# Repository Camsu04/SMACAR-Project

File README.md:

# SMACAR-Project 

**SMACAR: SISTEMA DE MONITOREO Y ALERTA DE CALIDAD DEL AGUA RURAL**

Plataforma distribuida de monitoreo de calidad de agua diseñada para entornos rurales: cada nodo utiliza un ESP32 programado íntegramente en C que adquiere parámetros críticos (pH, turbidez, conductividad y temperatura) mediante sensores industriales. La comunicación se realiza vía LoRaWAN, asegurando transmisión de datos robusta, segura y de largo alcance hacia una interfaz web/móvil de acceso remoto. El sistema opera con energía renovable, priorizando autonomía y bajo mantenimiento. El diseño prioriza robustez, escalabilidad y validación científica, permitiendo despliegue inmediato, integración con infraestructuras existentes y generación automatizada de alertas para respuesta temprana ante riesgos sanitarios.

---

## 🌟 Vista rápida

### Diseño del sistema

---

### Prototipo físico armado

Coming soon...
// 

---

### Electronica

| PCB TRANSMISOR                            | PCB RECEPTOR                               |
|-------------------------------------------|--------------------------------------------|
|  |  |

---

### Carcasa 3D 

| Transmisor y sensores                     | RECEPTOR                                   |
|-------------------------------------------|--------------------------------------------|
|  |  |

---

### Diseño 3D animado

---

### App móvil

| Pantalla principal | App en funcionamiento |
|--------------------|----------------------|
|  |  |

### DASHBOARD WEB

---

### Diagrama de Flujo

| Transmisor | Receptor                     |
|--------------------|----------------------|
| .png) | .png) |

---

## 📁 Estructura del repositorio

```
SMACAR-Project/
├── Documentacion/           # Diagramas, fotos y GIFs de diseño
│   ├── Layout.png
│   ├── CARCASA.jpg
│   ├── DIAGRAMA.pdf
│   ├── DATASHEET.pdf
│   ├── PROYECTO FINAL.jpg
├── Hardware/                # Archivos y esquemas electrónicos + Diseños 3d en solidworks
├── Software firmware/       # Código fuente para ESP32 y LoRa
├── mobile app/              # Capturas de la app móvil
│   ├── APP.jpg
│   ├── APP MOBILE EN FUNCIONAMIENTO.jpg
├── LICENSE
└── README.md
```

---

## 🚀 ¿Cómo empezar?

1. **Clona el repositorio:**
    ```bash
    git clone https://github.com/Camsu04/SMACAR-Project.git
    cd SMACAR-Project
    ```

2. **Revisa los esquemas y fotos** en la carpeta `Documentacion/`.

3. **Carga el firmware** desde `Software firmware/` a tu ESP32 usando [ESP-IDF](https://docs.espressif.com/projects/esp-idf/en/latest/esp32/get-started/index.html).

4. **Configura los sensores** (pH, turbidez, TDS) según el diseño mostrado y alimenta el sistema (idealmente con energía solar).

5. **Visualiza los datos** usando la app móvil incluida.

---

## ⚡ Características

- Sistema modular, autónomo y robusto
- Monitoreo de agua en tiempo real
- Notificaciones y visualización desde tu móvil
- Carcasa resistente impresa en 3D
- Bajo consumo y operación solar
- Fácil de instalar y ampliar

---

## 🛠️ Requisitos

- **ESP32**
- Sensores de pH, turbidez,temperatura y TDS
- Módulo LoRa (compatible ESP32)
- Fuente solar o alimentación adecuada (3.3v o 5v)
- Teléfono Android para la app móvil

---

## 📲 App móvil

Encuentra las capturas y funcionamiento en la carpeta `mobile app/`.
La app permite visualizar datos de los sensores, recibir alertas y consultar el historial.

---

## 🤝 Contribuciones

¿Tienes ideas o mejoras?
- Abre un *Issue* para dudas o bugs
- Haz un *Pull Request* si mejoras el código, documentación o la app móvil

---

## 📄 Licencia

Proyecto bajo licencia MIT.
Consulta el archivo [LICENSE](LICENSE).

---

## 👨‍💻 Autores

- [Camsu04](https://github.com/Camsu04)
- [Fausto123f](https://github.com/Fausto123f)
- [j0nfut](https://github.com/j0nfut)
- [RiQ4](https://github.com/RiQ4)

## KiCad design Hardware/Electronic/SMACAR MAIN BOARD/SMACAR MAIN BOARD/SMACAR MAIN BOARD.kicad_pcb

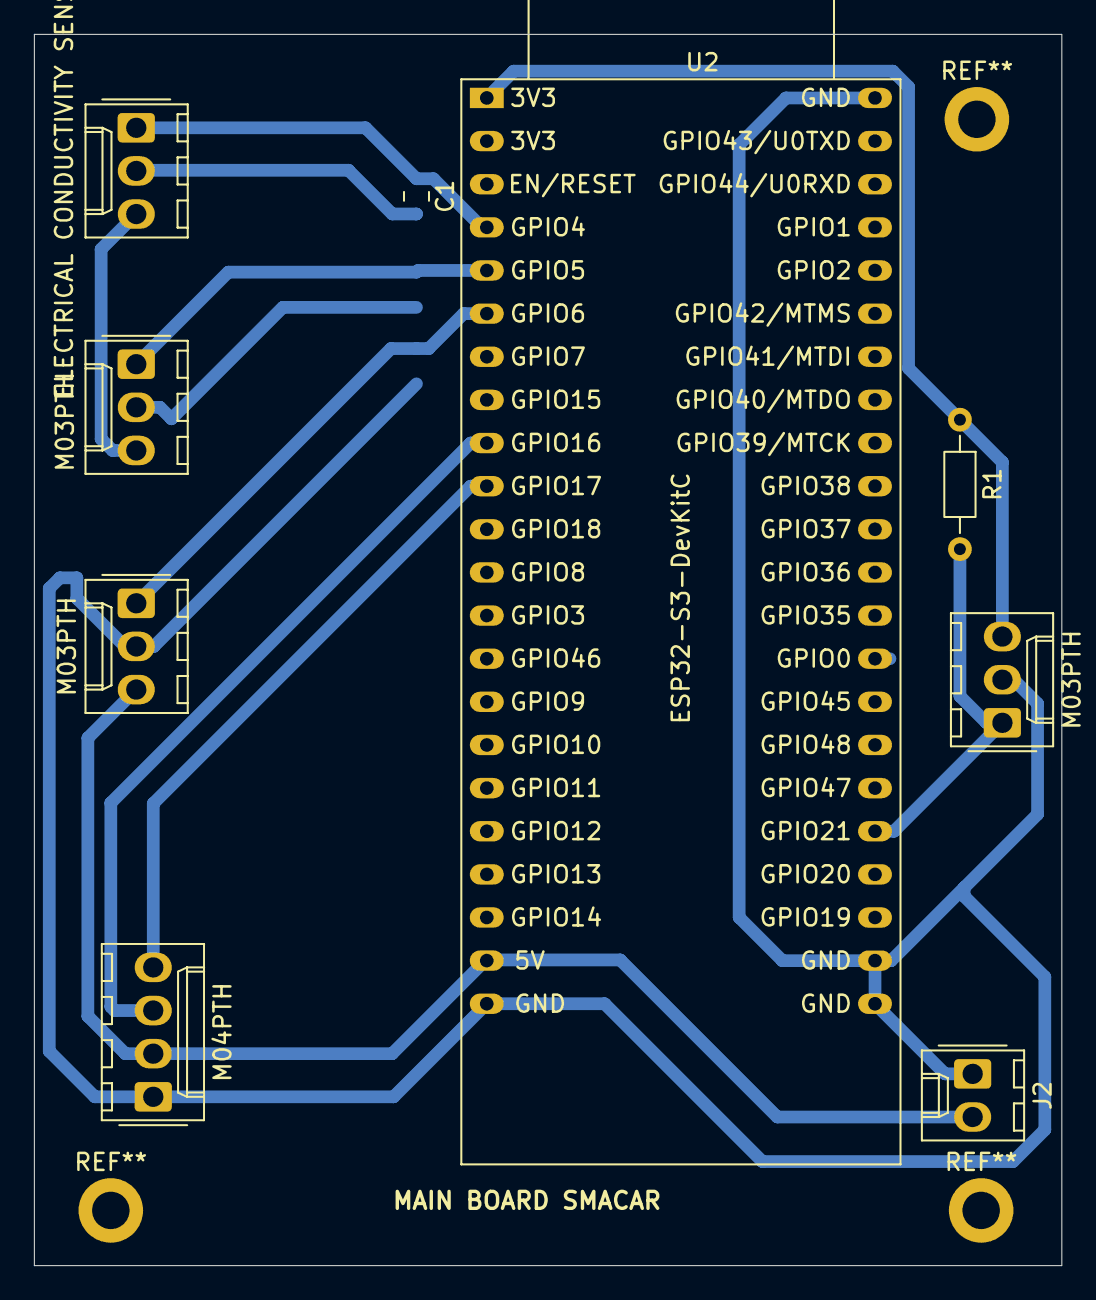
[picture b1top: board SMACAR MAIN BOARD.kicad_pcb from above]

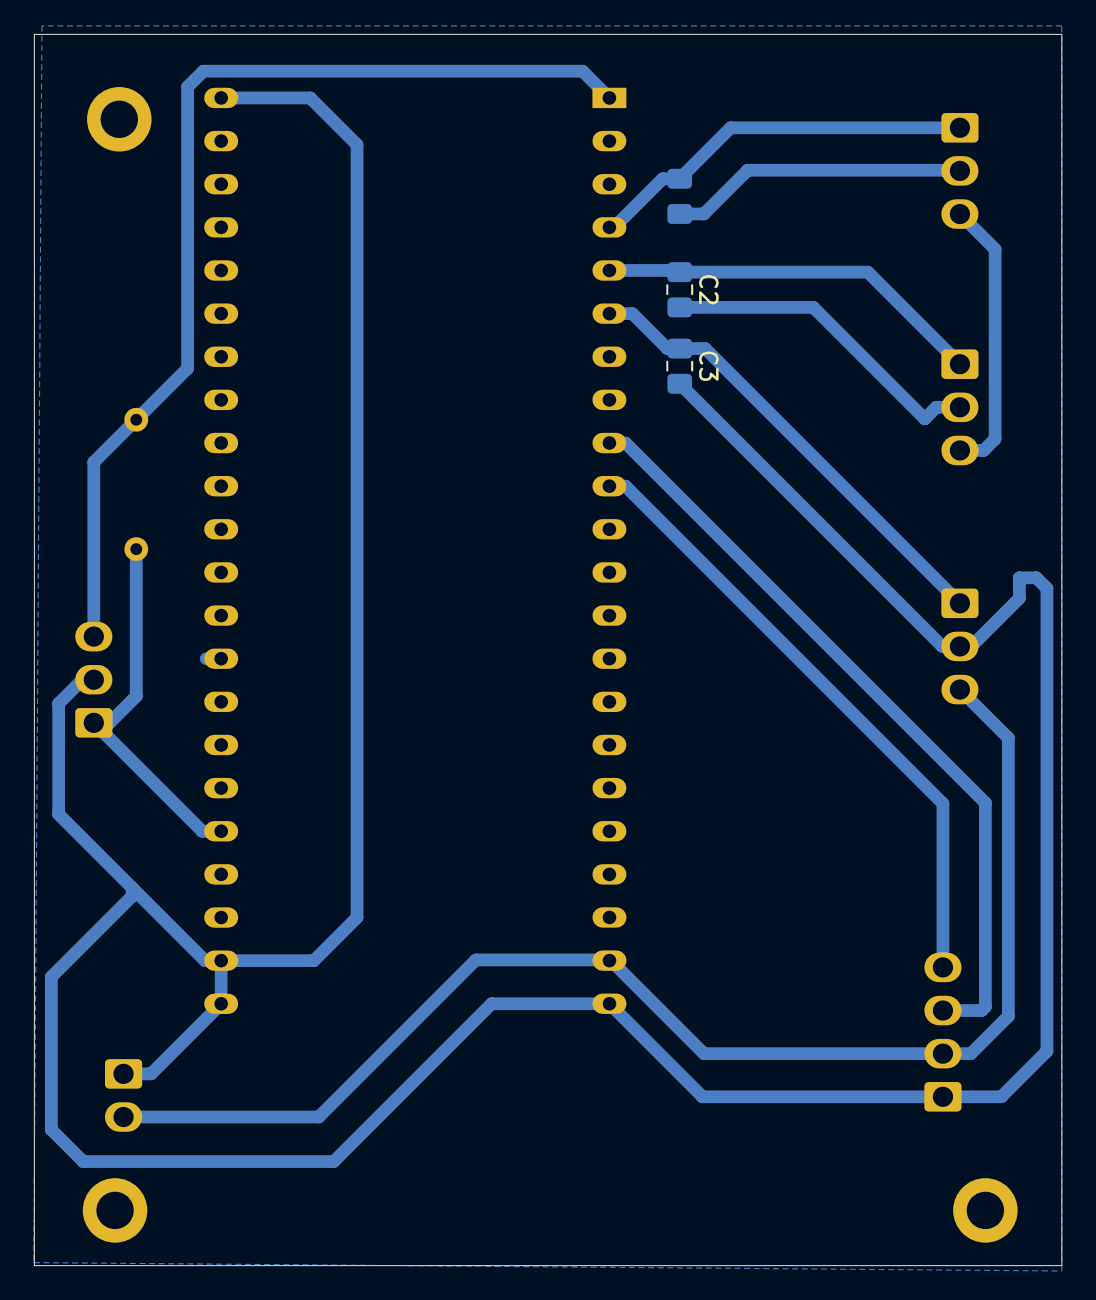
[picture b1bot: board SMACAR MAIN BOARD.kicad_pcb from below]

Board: 2 copper layers, 60.5 x 72.5 mm, 11 parts (2 on the bottom side), 9 nets.

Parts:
C1, C2, C3: 100nF_Ceramic; C_0805_2012Metric_Pad1.18x1.45mm_HandSolder
J2: Conn_01x02; Molex_KK-254_AE-6410-02A_1x02_P2.54mm_Vertical
MOLEX1: ELECTRICAL CONDUCTIVITY SENSOR; Molex_KK-254_AE-6410-03A_1x03_P2.54mm_Vertical
MOLEX2, MOLEX3, MOLEX4: M03PTH; Molex_KK-254_AE-6410-03A_1x03_P2.54mm_Vertical
MOLEX5: M04PTH; Molex_KK-254_AE-6410-04A_1x04_P2.54mm_Vertical
R1: 4.7k; R_Axial_DIN0204_L3.6mm_D1.6mm_P7.62mm_Horizontal
U2: ESP32-S3-DevKitC

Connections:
3.3V: MOLEX4.3, R1.1, U2.1 (3V3), U2.2 (3V3)
5V: J2.2, MOLEX1.3, MOLEX2.3, MOLEX3.3, MOLEX5.2, U2.21 (5V)
ELECTRICAL CONDUCTIVITY: C1.1, MOLEX1.1, U2.4 (GPIO4/ADC1_CH3)
GND: C1.2, C2.2, C3.2, J2.1, MOLEX1.2, MOLEX2.2, MOLEX3.2, MOLEX4.2, MOLEX5.1, U2.22 (GND), U2.23 (GND), U2.24 (GND), U2.44 (GND)
PH SENSOR: C2.1, MOLEX2.1, U2.5 (GPIO5/ADC1_CH4)
RX: MOLEX5.3, U2.9 (GPIO16/ADC2_CH5/32K_N)
TDS SENSOR: C3.1, MOLEX3.1, U2.6 (GPIO6/ADC1_CH5)
TEMP SENSOR: MOLEX4.1, R1.2, U2.27 (GPIO21)
Tx: MOLEX5.4, U2.10 (GPIO17/ADC2_CH6)

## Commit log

2025-05-19 Update LICENSE
2025-05-21 Documentacion de sensores y power manager
2025-05-25 Main BOARD Transmisora
2025-05-25 upgrade
2025-05-25 Placa Terminada y Revisada por Camila Fernandez
2025-05-26 Arreglo de Antena del esp32
2025-05-26 Arreglo de Pista GPIO21
2025-05-26 Gerber
2025-05-26 Diagrama
2025-05-26 Placa receptora de datos de los sensores
2025-05-26 arreglos en las conexiones de usb c
2025-05-26 PCB LAYOUT
2025-05-26 diagrama de placa secundaria
2025-06-05 RESISTENCIA PULL DOWN 5.1K
2025-06-18 Main Board Update
    PCB Fix and Fabrication files generated
2025-06-18 V1.0 Revision
    Revision for V1.0 of the project. Includes production files for JLCPCB. Some footprints and schematic symbols were changed.
2025-06-21 Create p
2025-06-23 ORGANIZACION
    ORGANIZANDO LOS ARCHIVOS
2025-06-23 Check
2025-07-23 update
    PCB Y CODIGO PROTOTIPO
2025-08-05 aaaaaaaaaaaaaaaaaa
2025-08-06 Firmware Transmisor listo
    Camila+Eric
2025-08-06 eliminando basura
2025-08-06 Firmware Transmisor y Receptor 90%
    Eric + Camila
2025-08-06 Arreglo 3D design
2025-08-06 Transmisor 100% y Receptor listo para la fase de interfaz grafica
    Besto
2025-08-06 3D corregido
2025-08-07 Firmware terminado y Interfaz de usuario 95%
    Perfecto todo
2025-08-07 Rename APP MOBILE EN FUNCIONAMIENTO.jpg to APP_MOBILE_EN_FUNCIONAMIENTO.jpg
2025-08-07 Rename APP.jpg to APP_fuera.jpg
2025-08-07 Rename ChatGPT Image 7 ago 2025, 18_46_12.png to logo.png
2025-08-07 PCB RECEPTOR MODIFICADA
2025-08-08 cosillas
2025-08-08 aaaaaaaaaa
2025-08-08 AAAAAAAAAAAAAA
2025-08-08 receptor
2025-08-08 PCBS
2025-08-08 Rename Diagrama.png to Diagrama1.png
2025-08-08 aaaa
2025-08-08 receptor 100%
2025-08-08 bueno
2025-08-08 Diagrama de flujo
2025-08-09 Cami me tiene harto ;3
2025-08-16 Hola
2025-08-16 arreglando cositas
2025-08-19 carcasa
